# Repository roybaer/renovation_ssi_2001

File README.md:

# Renovation SSI-2001

This repository contains the design files for the _Renovation SSI-2001_ sound card, a replica of the _Innovation SSI-2001_ with some unobtrusive modifications that eliminate the dependency on vintage parts.
The Innovation SSI-2001 was an 8-bit ISA sound card from the late 1980s that was based on Commodore's SID synthesizer chip.

This modified design can optionally use an STM32 microcontroller, instead.
It can also use two NE556 dual timer ICs instead of a single NE558 quad timer IC for the integrated analog joystick interface.
All optional modern replacement components share the location of the vintage parts they replace, so that the modifications are largely invisible in combination with vintage parts.

## Front view

This picture shows the front of the card.

There is also a picture of the [back side of the card](img/photo_back.jpg).

## Optional vintage components

You will need the following vintage components for a visually accurate replica:

- A SID chip (MOS 6581 or MOS 8580, the latter with a hidden voltage regulator)
- An NE558 quad timer IC for the joystick interface

## Bill of materials

The design files of this project combine multiple possible hardware configurations in the same schematic diagram and PCB layout.
Hence, the unmodified tool-generated BOM will not yield a sensible hardware configuration.
Please read the notes in the schematic diagram, decide which variant you want to build and adjust the BOM, accordingly.

## Configuration

Please consult the [settings document](doc/settings.md) for jumper settings.

## Additional notes

The planned adaptation of the [STM32-SID-PLAYER](https://github.com/Bakisha/STM32-SID-PLAYER) firmware for this card, i.e. the implementation of an ISA interface for the synthesizer core is still pending.
Right now, this card is therefore only usable in combination with either an original SID or a modern substitute like the SwinSID.

The exact DA15 and RCA connectors found on the original card are no longer available and have therefore been replaced by affordable modern variants.
Furthermore, the RCA jack and the mounting holes have been shifted to simplify the adaptation of the generic Keystone 9202 ISA bracket.

## License

The following license applies to the files in this repository:

This work is licensed under the Creative Commons Attribution-ShareAlike 4.0 International License. To view a copy of this license, visit http://creativecommons.org/licenses/by-sa/4.0/ or send a letter to Creative Commons, PO Box 1866, Mountain View, CA 94042, USA.

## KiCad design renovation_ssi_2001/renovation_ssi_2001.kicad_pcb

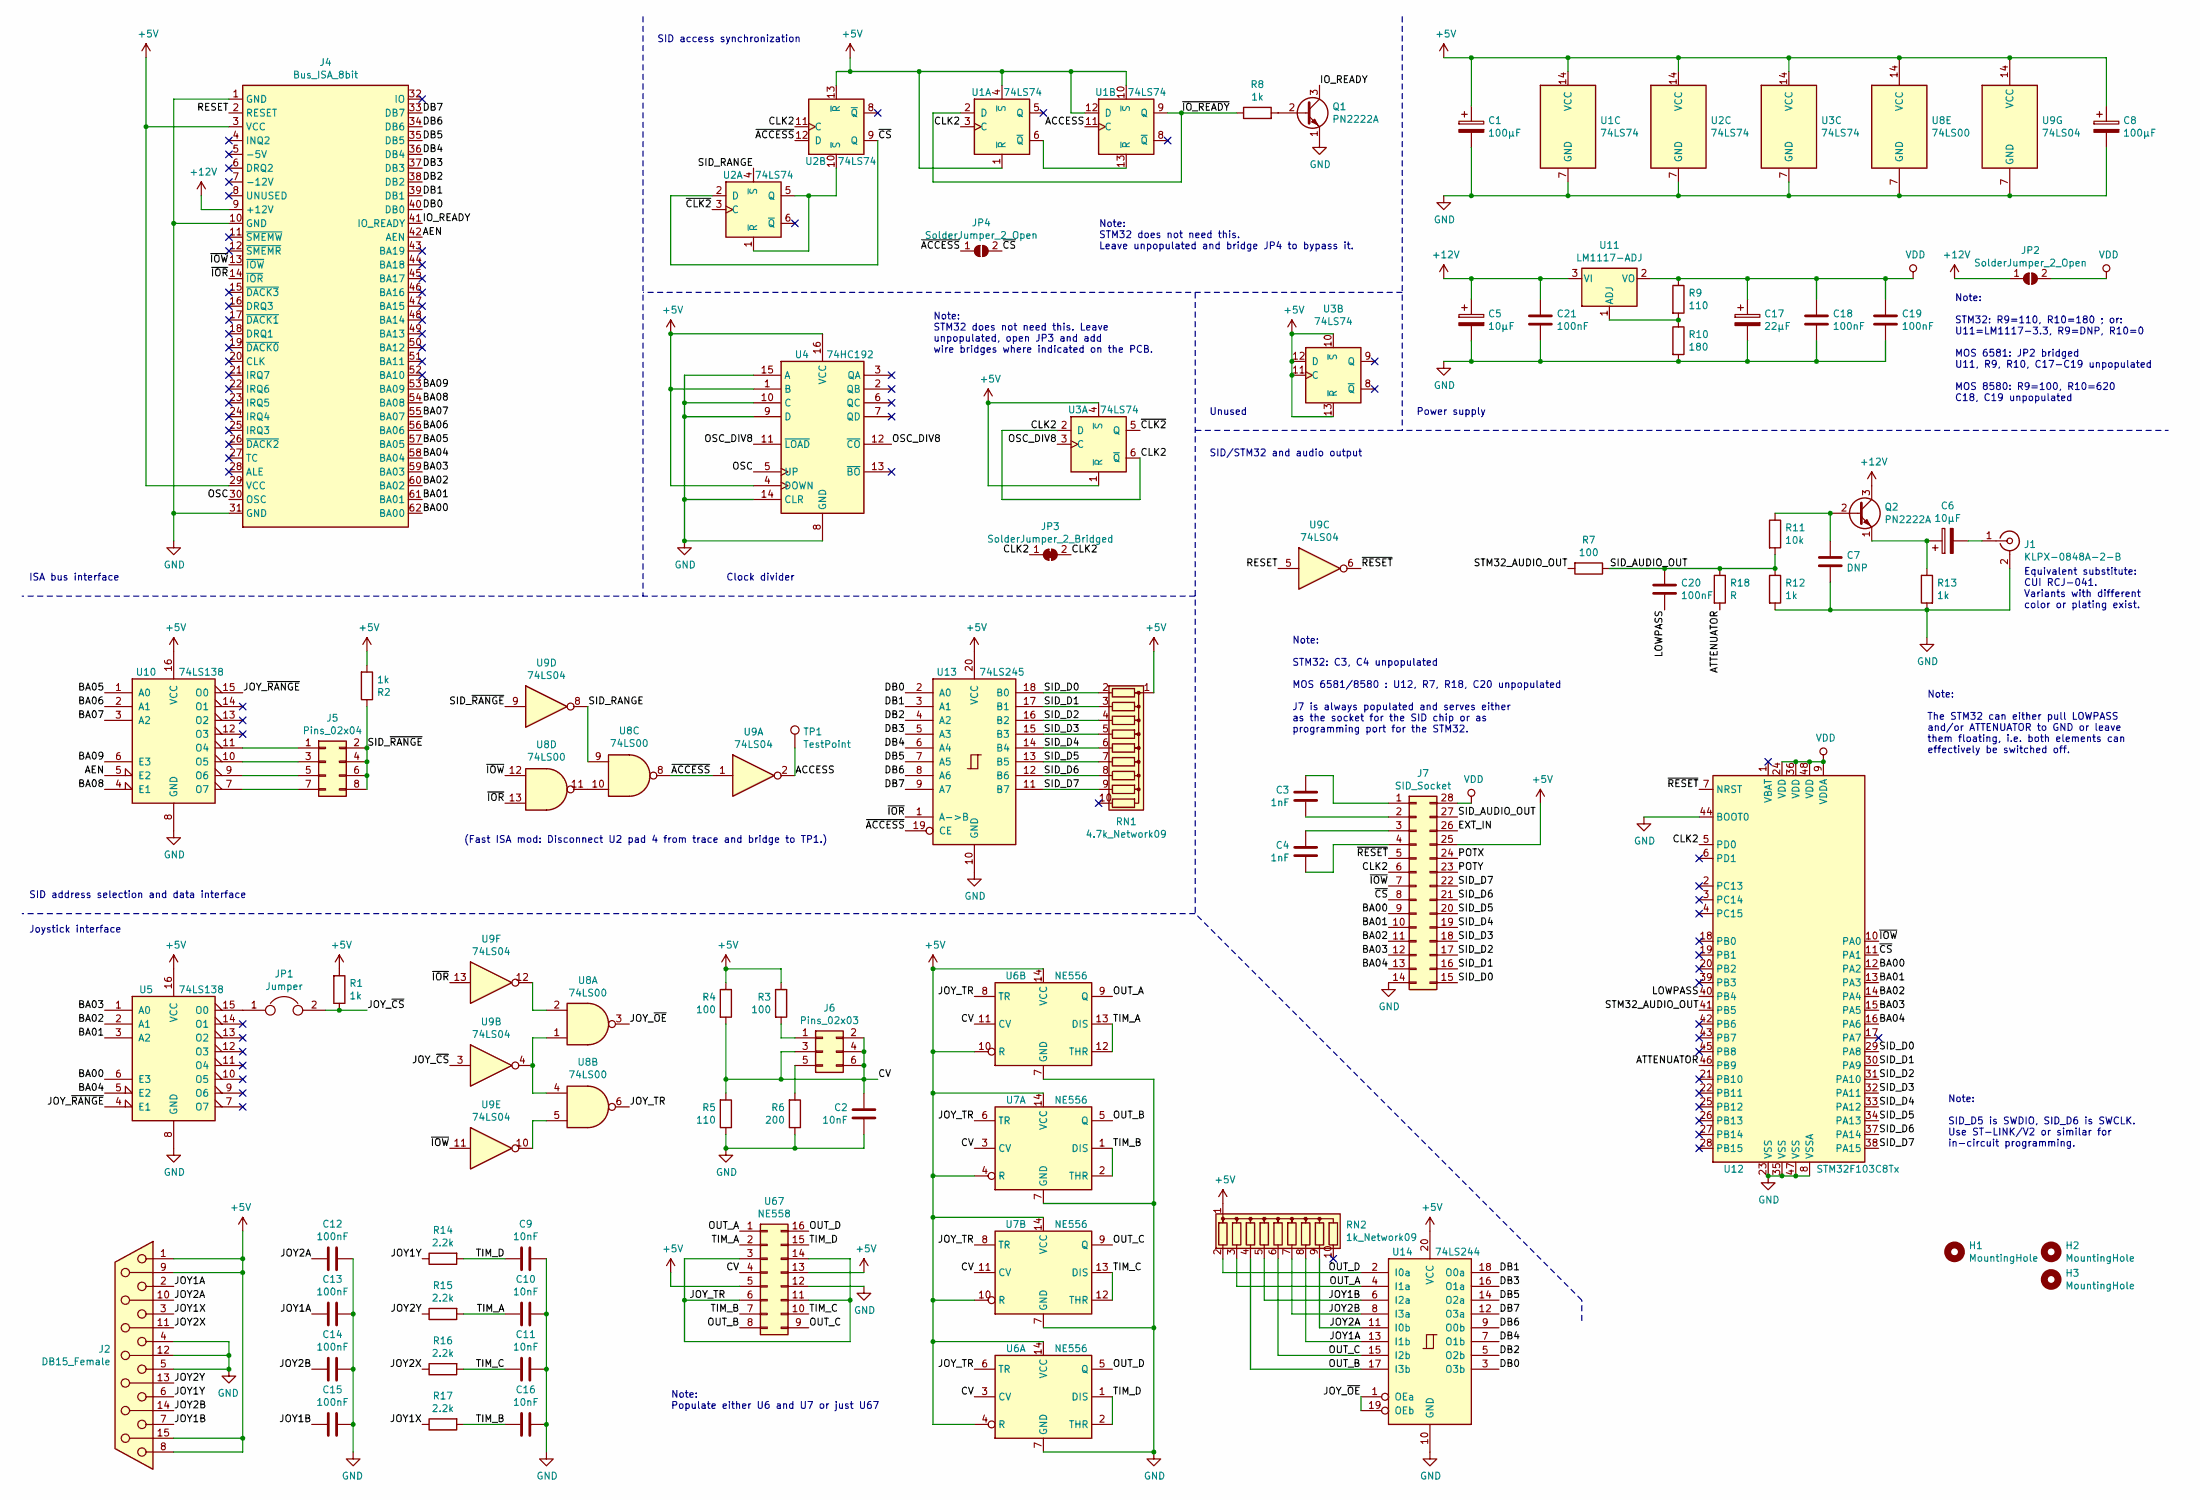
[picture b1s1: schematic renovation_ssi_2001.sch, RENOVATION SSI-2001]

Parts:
C1, C8: 100µF; CP_Radial_D6.3mm_P2.50mm
C2, C9, C10, C11, C16: 10nF; C_Disc_D3.4mm_W2.1mm_P2.50mm
C3, C4: 1nF; C_Disc_D3.4mm_W2.1mm_P2.50mm
C5, C6: 10µF; CP_Axial_L11.0mm_D5.0mm_P18.00mm_Horizontal
C7: DNP; C_Disc_D3.4mm_W2.1mm_P2.50mm_alt
C12, C13, C14, C15: 100nF; C_Disc_D3.4mm_W2.1mm_P2.50mm
C17: 22µF; CP_EIA-3528-21_Kemet-B
C18, C19, C20, C21: 100nF; C_0603_1608Metric
H1, H2, H3: MountingHole; MountingHole_3.2mm_M3
J1: KLPX-0848A-2-B; Cinch_Kycon_KLPX-0848A-2-B
J2: DB15_Female; DSUB-15_Female_Horizontal_P2.77x2.84mm_EdgePinOffset7.70mm_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
J4: Bus_ISA_8bit; BUS_XT
J5: Pins_02x04; PinHeader_2x04_P2.54mm_Vertical
J6: Pins_02x03; PinHeader_2x03_P2.54mm_Vertical
J7: SID_Socket; DIP-28_W15.24mm
JP1: Jumper; PinHeader_1x02_P2.54mm_Vertical
JP2, JP4: SolderJumper_2_Open; SolderJumper-2_P1.3mm_Open_RoundedPad1.0x1.5mm
JP3: SolderJumper_2_Bridged; SolderJumper-2_P1.3mm_Bridged_RoundedPad1.0x1.5mm
Q1, Q2: PN2222A; TO-92
R1, R2, R8, R12, R13: 1k; R_Axial_DIN0309_L9.0mm_D3.2mm_P12.70mm_Horizontal
R3, R4: 100; R_Axial_DIN0309_L9.0mm_D3.2mm_P12.70mm_Horizontal
R5: 110; R_Axial_DIN0309_L9.0mm_D3.2mm_P12.70mm_Horizontal
R6: 200; R_Axial_DIN0309_L9.0mm_D3.2mm_P12.70mm_Horizontal
R7: 100; R_0603_1608Metric
R9: 110; R_0603_1608Metric
R10: 180; R_0603_1608Metric
R11: 10k; R_Axial_DIN0309_L9.0mm_D3.2mm_P12.70mm_Horizontal
R14, R15, R16, R17: 2.2k; R_Axial_DIN0309_L9.0mm_D3.2mm_P12.70mm_Horizontal
R18: R; R_0603_1608Metric
RN1: 4.7k_Network09; R_Array_SIP10
RN2: 1k_Network09; R_Array_SIP10
TP1: TestPoint; TestPoint_Pad_1.5x1.5mm
U1, U2, U3: 74LS74; DIP-14_W7.62mm
U4: 74HC192; DIP-16_W7.62mm
U5, U10: 74LS138; DIP-16_W7.62mm
U6, U7: NE556; SSOP-14_5.3x6.2mm_P0.65mm
U8: 74LS00; DIP-14_W7.62mm
U9: 74LS04; DIP-14_W7.62mm
U11: LM1117-ADJ; SOT-223-3_TabPin2
U12: STM32F103C8Tx; LQFP-48_7x7mm_P0.5mm
U13: 74LS245; DIP-20_W7.62mm
U14: 74LS244; DIP-20_W7.62mm
U67: NE558; DIP-16_W7.62mm

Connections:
+5V: C1.1, C8.1, J2.1, J2.8, J2.9, J2.15, J4.3 (VCC), J4.29 (VCC), J7.25, R1.2, R2.2, R3.1, R4.1, RN1.1 (common), RN2.1 (common), U1.1 (~R), U1.4 (~S), U1.10 (~S), U1.12 (D), U1.14 (VCC), U2.13 (~R), U2.14 (VCC), U3.1 (~R), U3.4 (~S), U3.10 (~S), U3.11 (C), U3.12 (D), U3.13 (~R), U3.14 (VCC), U4.1 (B), U4.4 (DOWN), U4.16 (VCC), U5.16 (VCC), U6.4 (R), U6.10 (R), U6.14 (VCC), U7.4 (R), U7.10 (R), U7.14 (VCC), U8.14 (VCC), U9.14 (VCC), U10.16 (VCC), U13.20 (VCC), U14.20 (VCC), U67.5, U67.13
+12V: C5.1, C21.1, J4.9 (+12V), JP2.1 (A), Q2.3 (C), U11.3 (VI)
/ACCESS: TP1.1, U1.11 (C), U9.2
/AEN: J4.42 (AEN), U10.5 (E2)
/ATTENUATOR: R18.2, U12.46 (PB9)
/BA00: J4.62 (BA00), J7.9, U5.6 (E3), U12.12 (PA2)
/BA01: J4.61 (BA01), J7.10, U5.3 (A2), U12.13 (PA3)
/BA02: J4.60 (BA02), J7.11, U5.2 (A1), U12.14 (PA4)
/BA03: J4.59 (BA03), J7.12, U5.1 (A0), U12.15 (PA5)
/BA04: J4.58 (BA04), J7.13, U5.5 (E2), U12.16 (PA6)
/BA05: J4.57 (BA05), U10.1 (A0)
/BA06: J4.56 (BA06), U10.2 (A1)
/BA07: J4.55 (BA07), U10.3 (A2)
/BA08: J4.54 (BA08), U10.4 (E1)
/BA09: J4.53 (BA09), U10.6 (E3)
/CLK2: J7.6, JP3.1 (A), JP3.2 (B), U1.3 (C), U2.11 (C), U3.2 (D), U3.6 (~Q), U12.5 (PD0)
/CV: C2.1, J6.2, J6.3, J6.4, J6.6, R4.2, R5.2, U6.3 (CV), U6.11 (CV), U7.3 (CV), U7.11 (CV), U67.4
/DB0: J4.40 (DB0), U13.2 (A0), U14.3 (O3b)
/DB1: J4.39 (DB1), U13.3 (A1), U14.18 (O0a)
/DB2: J4.38 (DB2), U13.4 (A2), U14.5 (O2b)
/DB3: J4.37 (DB3), U13.5 (A3), U14.16 (O1a)
/DB4: J4.36 (DB4), U13.6 (A4), U14.7 (O1b)
/DB5: J4.35 (DB5), U13.7 (A5), U14.14 (O2a)
/DB6: J4.34 (DB6), U13.8 (A6), U14.9 (O0b)
/DB7: J4.33 (DB7), U13.9 (A7), U14.12 (O3a)
/EXT_IN: J7.26
/IO_READY: J4.41 (IO_READY), Q1.3 (C)
/JOY1A: C13.2, J2.2, RN2.8 (R7), U14.13 (I1b)
/JOY1B: C15.2, J2.7, RN2.5 (R4), U14.6 (I2a)
/JOY1X: J2.3, R17.1
/JOY1Y: J2.6, R14.1
/JOY2A: C12.2, J2.10, RN2.9 (R8), U14.11 (I0b)
/JOY2B: C14.2, J2.14, RN2.7 (R6), U14.8 (I3a)
/JOY2X: J2.11 (P111), R16.1
/JOY2Y: J2.13, R15.1
/JOY_TR: U6.6 (TR), U6.8 (TR), U7.6 (TR), U7.8 (TR), U8.6, U67.3, U67.6, U67.11, U67.14
/JOY_~CS: JP1.2, R1.1, U9.3
/JOY_~OE: U8.3, U14.1 (OEa), U14.19 (OEb)
/JOY_~RANGE: U5.4 (E1), U10.15 (O0)
/LOWPASS: C20.2, U12.40 (PB4)
/OSC: J4.30 (OSC), U4.5 (UP)
/OSC_DIV8: U3.3 (C), U4.11 (~LOAD), U4.12 (~CO)
/OUT_A: RN2.3 (R2), U6.9 (Q), U14.4 (I1a), U67.1
/OUT_B: RN2.4 (R3), U7.5 (Q), U14.17 (I3b), U67.8
/OUT_C: RN2.6 (R5), U7.9 (Q), U14.15 (I2b), U67.9
/OUT_D: RN2.2 (R1), U6.5 (Q), U14.2 (I0a), U67.16
/POTX: J7.24
/POTY: J7.23
/RESET: J4.2 (RESET), U9.5
/SID_AUDIO_OUT: C20.1, J7.27, R7.1, R11.2, R12.1, R18.1
/SID_D0: J7.15, RN1.2 (R1), U12.29 (PA8), U13.18 (B0)
/SID_D1: J7.16, RN1.3 (R2), U12.30 (PA9), U13.17 (B1)
/SID_D2: J7.17, RN1.4 (R3), U12.31 (PA10), U13.16 (B2)
/SID_D3: J7.18, RN1.5 (R4), U12.32 (PA11), U13.15 (B3)
/SID_D4: J7.19, RN1.6 (R5), U12.33 (PA12), U13.14 (B4)
/SID_D5: J7.20, RN1.7 (R6), U12.34 (PA13), U13.13 (B5)
/SID_D6: J7.21, RN1.8 (R7), U12.37 (PA14), U13.12 (B6)
/SID_D7: J7.22, RN1.9 (R8), U12.38 (PA15), U13.11 (B7)
/SID_RANGE: U2.4 (~S), U8.9, U9.8
/SID_~RANGE: J5.2, J5.4, J5.6, J5.8, R2.1, U9.9
/STM32_AUDIO_OUT: R7.2, U12.41 (PB5)
/TIM_A: C10.1, R15.2, U6.12 (THR), U6.13 (DIS), U67.2
/TIM_B: C16.1, R17.2, U7.1 (DIS), U7.2 (THR), U67.7
/TIM_C: C11.1, R16.2, U7.12 (THR), U7.13 (DIS), U67.10
/TIM_D: C9.1, R14.2, U6.1 (DIS), U6.2 (THR), U67.15
/~ACCESS: JP4.1 (A), U2.12 (D), U8.8, U9.1, U13.19 (CE)
/~CLK2: U2.3 (C), U3.5 (Q)
/~CS: J7.8, JP4.2 (B), U2.2 (D), U2.9 (Q), U12.11 (PA1)
/~IOR: J4.14 (~IOR), U8.13, U9.13, U13.1 (A->B)
/~IOW: J4.13 (~IOW), J7.7, U8.12, U9.11, U12.10 (PA0)
/~IO_READY: R8.1, U1.2 (D), U1.9 (Q)
/~RESET: J7.5, U9.6, U12.7 (NRST)
GND: C1.2, C2.2, C5.2, C7.1, C8.2, C9.2, C10.2, C11.2, C12.1, C13.1, C14.1, C15.1, C16.2, C17.2, C18.2, C19.2, C21.2, J1.2 (Ext), J2.4, J2.5, J2.12, J4.1 (GND), J4.10 (GND), J4.31 (GND), J7.14, Q1.1 (E), R5.1, R6.1, R10.2, R12.2, R13.2, U1.7 (GND), U2.7 (GND), U3.7 (GND), U4.8 (GND), U4.9 (D), U4.10 (C), U4.14 (CLR), U4.15 (A), U5.8 (GND), U6.7 (GND), U7.7 (GND), U8.7 (GND), U9.7 (GND), U10.8 (GND), U12.8 (VSSA), U12.23 (VSS), U12.35 (VSS), U12.44 (BOOT0), U12.47 (VSS), U13.10 (GND), U14.10 (GND), U67.12
unnamed: C3.1, J7.1
unnamed: C3.2, J7.2
unnamed: C4.1, J7.3
unnamed: C4.2, J7.4
unnamed: C6.1, Q2.1 (E), R13.1
unnamed: C6.2, J1.1 (In)
unnamed: C7.2, Q2.2 (B), R11.1
unnamed: J5.1, U10.11 (O4)
unnamed: J5.3, U10.10 (O5)
unnamed: J5.5, U10.9 (O6)
unnamed: J5.7, U10.7 (O7)
unnamed: J6.1, R3.2
unnamed: J6.5, R6.2
unnamed: JP1.1, U5.15 (O0)
unnamed: Q1.2 (B), R8.2
unnamed: R9.2, R10.1, U11.1 (ADJ)
unnamed: U1.6 (~Q), U1.13 (~R)
unnamed: U2.1 (~R), U2.5 (Q), U2.10 (~S)
unnamed: U8.1, U8.4, U9.4
unnamed: U8.2, U9.12
unnamed: U8.5, U9.10
unnamed: U8.10, U8.11
VDD: C17.1, C18.1, C19.1, J7.28, JP2.2 (B), R9.1, U11.2 (VO), U12.9 (VDDA), U12.24 (VDD), U12.36 (VDD), U12.48 (VDD)

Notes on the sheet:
Unused
Joystick interface
Power supply
SID access synchronization
SID address selection and data interface
Clock divider
ISA bus interface
SID/STM32 and audio output
Note: STM32: C3, C4 unpopulated MOS 6581/8580 : U12, R7, R18, C20 unpopulated J7 is always populated and serves either as the socket for the SID chip or as programming port for the STM32.
Note: Populate either U6 and U7 or just U67
Note: STM32 does not need this. Leave unpopulated and bridge JP4 to bypass it.
Note: STM32 does not need this. Leave unpopulated, open JP3 and add wire bridges where indicated on the PCB.
Note: The STM32 can either pull LOWPASS and/or ATTENUATOR to GND or leave them floating, i.e. both elements can effectively be switched off.
(Fast ISA mod: Disconnect U2 pad 4 from trace and bridge to TP1.)
Equivalent substitute: CUI RCJ-041. Variants with different color or plating exist.
Note: STM32: R9=110, R10=180 ; or: U11=LM1117-3.3, R9=DNP, R10=0 MOS 6581: JP2 bridged U11, R9, R10, C17-C19 unpopulated MOS 8580: R9=100, R10=620 C18, C19 unpopulated
Note: SID_D5 is SWDIO, SID_D6 is SWCLK. Use ST-LINK/V2 or similar for in-circuit programming.

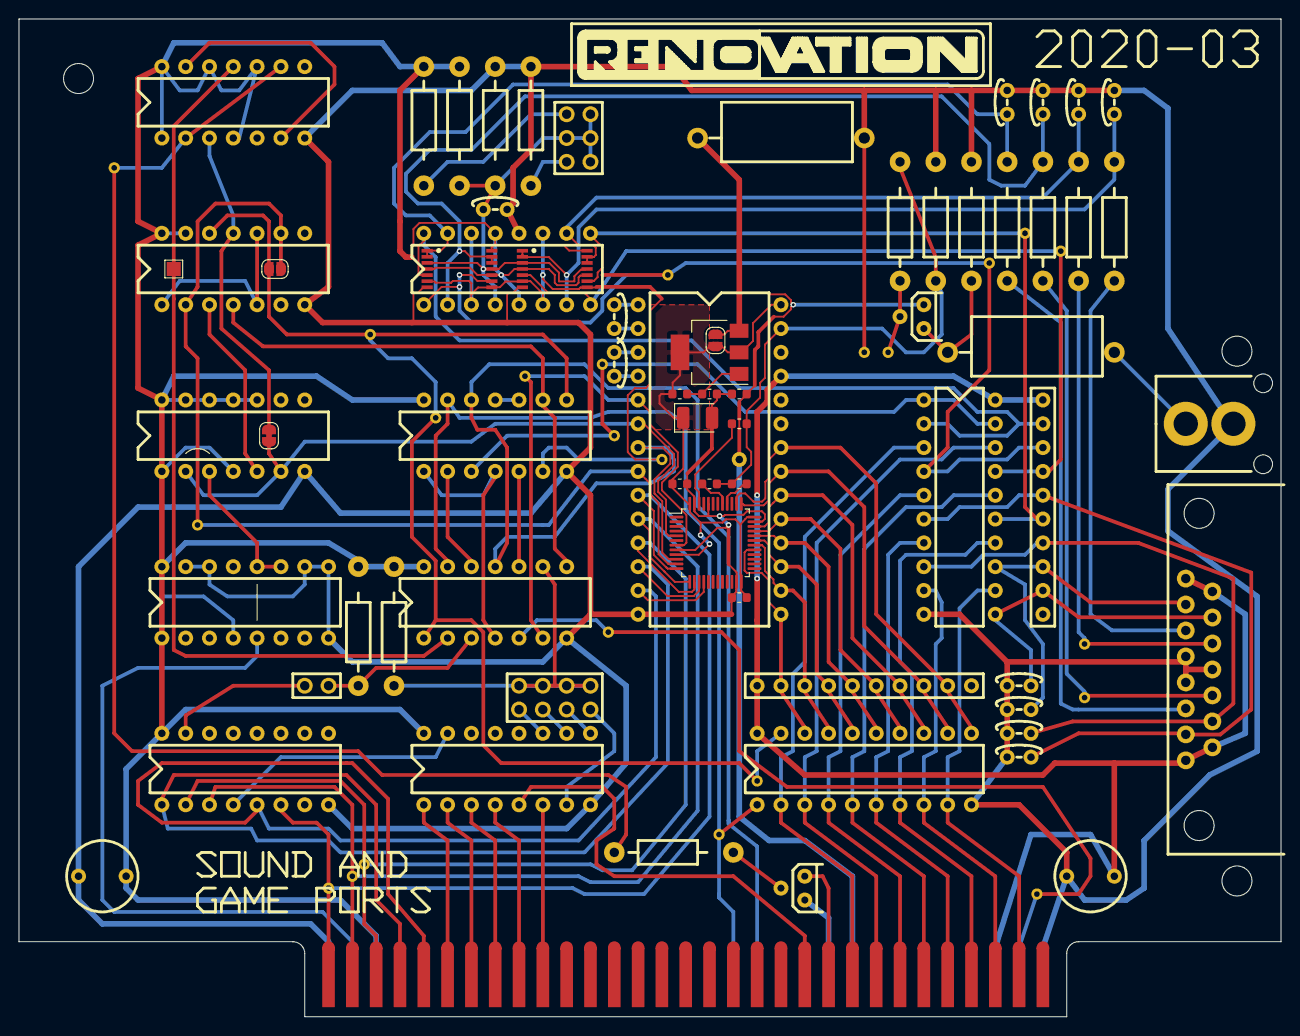
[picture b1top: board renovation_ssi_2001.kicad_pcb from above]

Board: 2 copper layers, 134.6 x 106.4 mm, 72 parts (0 on the bottom side), 93 nets.

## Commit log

2020-03-08 corrections and improvements
2020-03-10 fill in some component values, add pad to simplify fast ISA mod, adjust mounting hole positions
2020-03-13 correct configuration resistor values for the voltage regulator
2020-06-09 improve documentation
2020-07-26 add photos
2020-09-23 add additional notes
